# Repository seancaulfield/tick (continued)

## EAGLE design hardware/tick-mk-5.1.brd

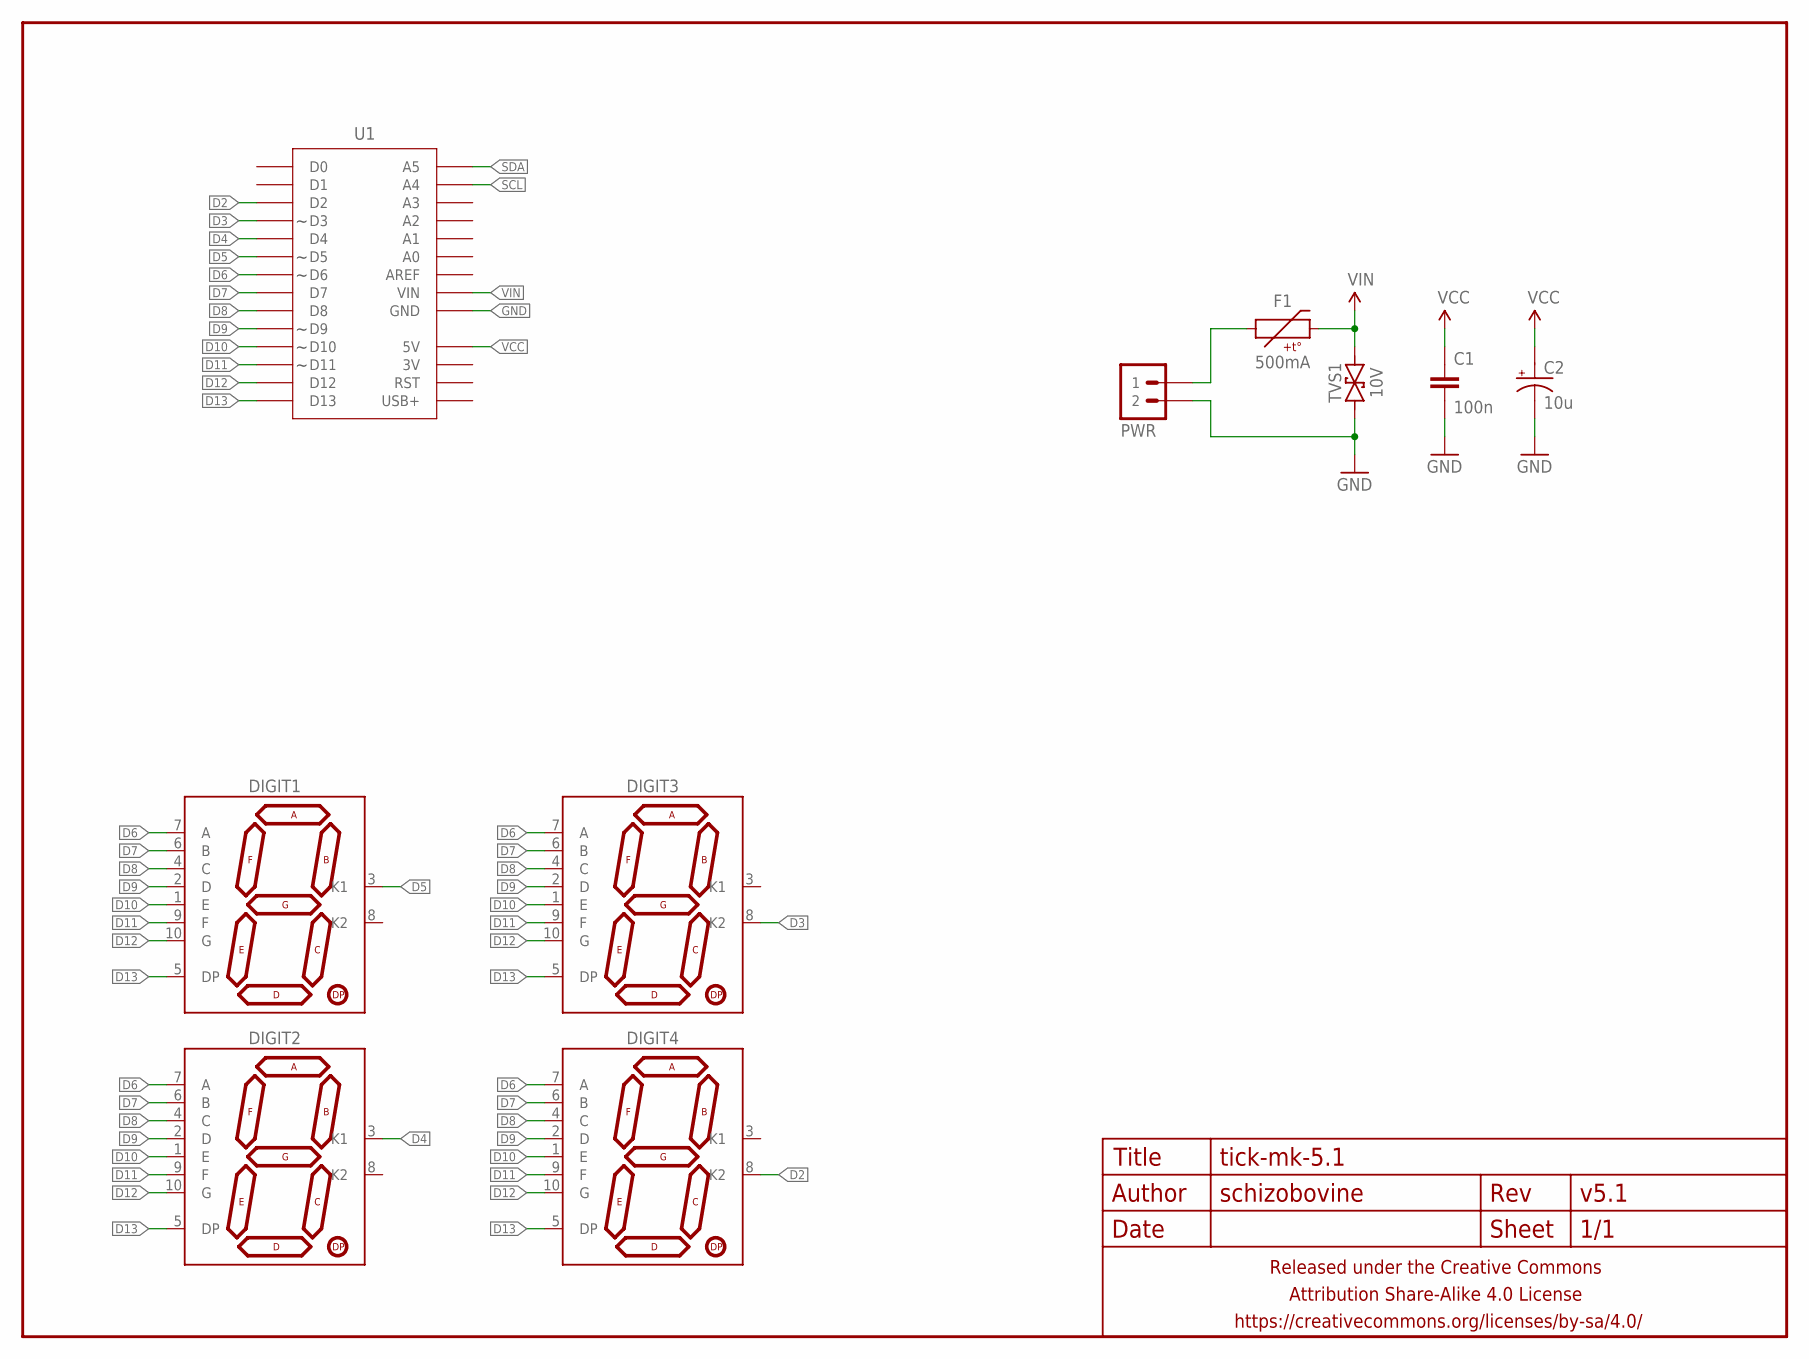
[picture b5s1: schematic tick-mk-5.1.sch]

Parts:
C1: 100n; C025-024X044
C2: 10u; E2-5
DIGIT1, DIGIT2, DIGIT3, DIGIT4: 7SEG_1DIGPTH-25.4MM-BARE; 7SEG_1DIG_25.4MM_NOSILK
F1: 500mA; PTC-PTH-5.08MM
FRAME1: FRAME-LETTERNO_PACKAGE; DUMMY
PWR: M02JST-PTH-VERT; JST-2-PH-VERT-PTH
TVS1: 10V; DO-41-TVS-BI-10.16MM
U1: ADAFRUIT_METRO_MININOHOLES-NOOUTLINE-SILK; ADAFRUIT_METRO_MINI

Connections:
D2: DIGIT4.8 (K2), U1.3 (D2)
D3: DIGIT3.8 (K2), U1.4 (D3)
D4: DIGIT2.3 (K1), U1.5 (D4)
D5: DIGIT1.3 (K1), U1.6 (D5)
D6: DIGIT1.7 (A), DIGIT2.7 (A), DIGIT3.7 (A), DIGIT4.7 (A), U1.7 (D6)
D7: DIGIT1.6 (B), DIGIT2.6 (B), DIGIT3.6 (B), DIGIT4.6 (B), U1.8 (D7)
D8: DIGIT1.4 (C), DIGIT2.4 (C), DIGIT3.4 (C), DIGIT4.4 (C), U1.9 (D8)
D9: DIGIT1.2 (D), DIGIT2.2 (D), DIGIT3.2 (D), DIGIT4.2 (D), U1.10 (D9)
D10: DIGIT1.1 (E), DIGIT2.1 (E), DIGIT3.1 (E), DIGIT4.1 (E), U1.11 (D10)
D11: DIGIT1.9 (F), DIGIT2.9 (F), DIGIT3.9 (F), DIGIT4.9 (F), U1.12 (D11)
D12: DIGIT1.10 (G), DIGIT2.10 (G), DIGIT3.10 (G), DIGIT4.10 (G), U1.13 (D12)
D13: DIGIT1.5 (DP), DIGIT2.5 (DP), DIGIT3.5 (DP), DIGIT4.5 (DP), U1.14 (D13)
GND: C1.2, C2.-, PWR.2, TVS1.P$1 (1), U1.19 (GND), U1.20 (GND)
unnamed: F1.P$1 (1), PWR.1
SCL: U1.27 (A4)
SDA: U1.28 (A5)
VCC: C1.1, C2.+, U1.18 (5V)
VIN: F1.P$2 (2), TVS1.P$2 (2), U1.21 (VIN)

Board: 2 copper layers, 15 parts (5 on the bottom side), 16 nets, no tracks yet.

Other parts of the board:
U$1: TICK_SYMBOL
U$2: COW_SMALL
U$4: CC-BY-SA-4.0-NO-URL
U$5: OSHWLOGO_TOP_0.2

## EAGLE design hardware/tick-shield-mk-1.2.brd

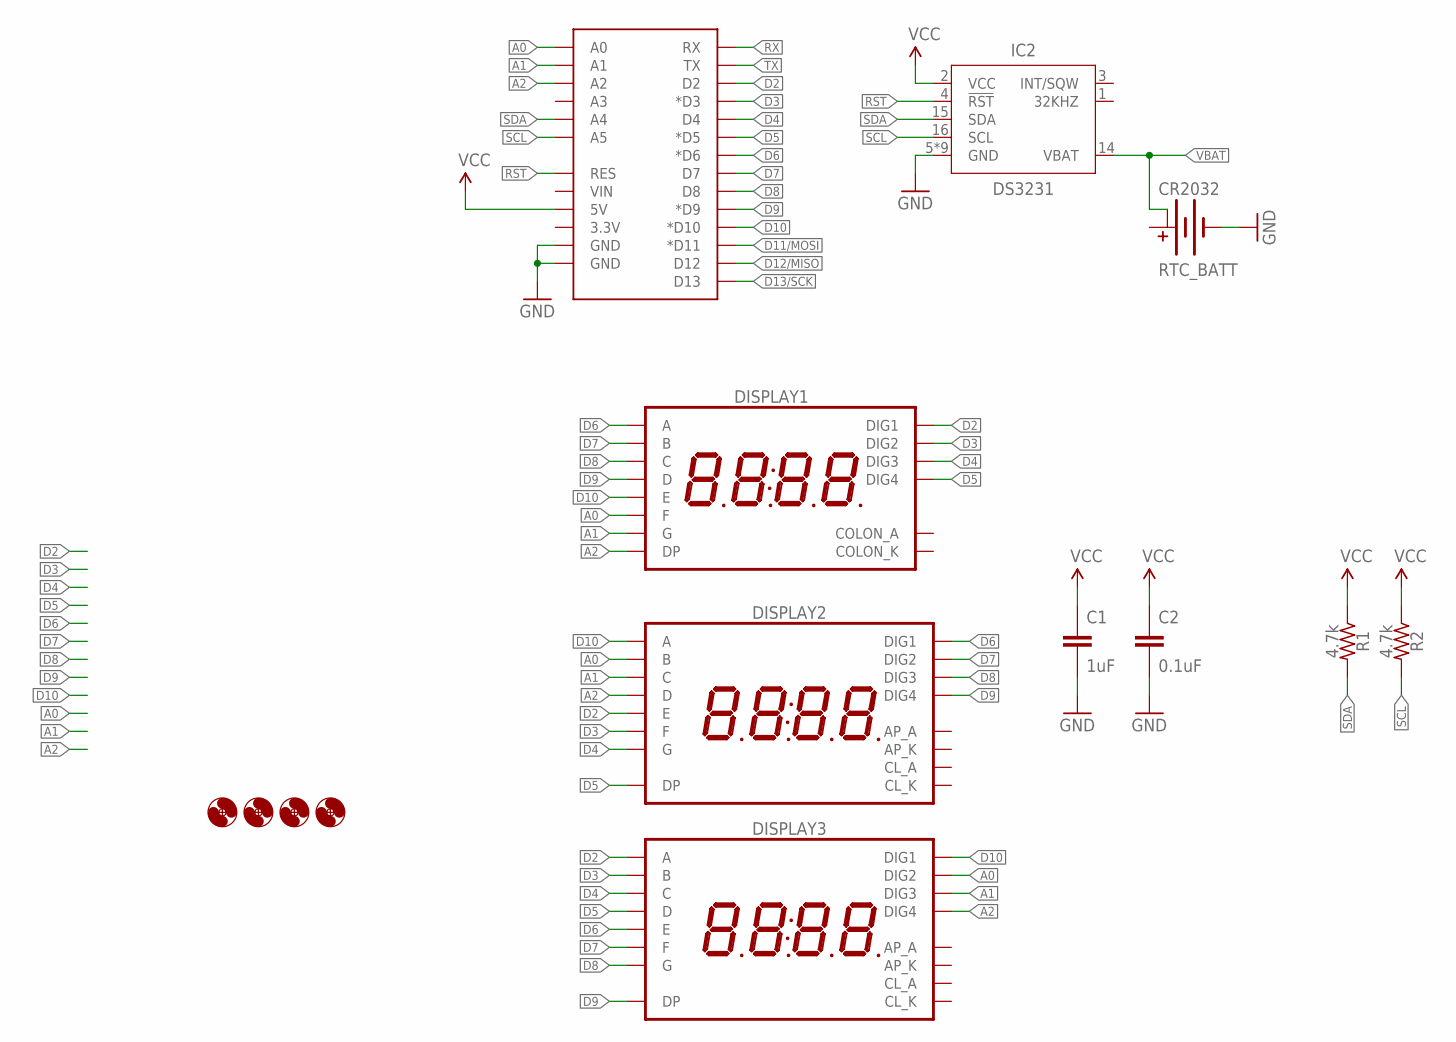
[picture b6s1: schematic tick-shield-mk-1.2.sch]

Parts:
C1: 1uF; C025-024X044
C2: 0.1uF; C0805
DISPLAY1: 7SEG_4DIGIT_COLON14.2MM-CC-NS; 7SEG_4DIG_NS
DISPLAY2, DISPLAY3: 7SEG_4DIGIT_COLON_APOS; 7SEG_4DIG_10MM
H1, H2, H3, H4: HOLE#2; HOLE-#2
IC2: DS3231; SO16W
R1, R2: 4.7k; RESISTOR-AXIAL-PTH-6.35MM
RTC_BATT: CR2032; BATTCON_20MM_MINE
U$1: ARDUINO_SHIELD_SMALLER; ARDUINO_SHIELD_NOOUTLINE_INSIDE_SMALLER

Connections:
A0: DISPLAY1.P$12 (F), DISPLAY2.16 (B), DISPLAY3.2 (DIG2), U$1.A0
A1: DISPLAY1.P$5 (G), DISPLAY2.13 (C), DISPLAY3.6 (DIG3), U$1.A1
A2: DISPLAY1.P$3 (DP), DISPLAY2.3 (D), DISPLAY3.8 (DIG4), U$1.A2
D2: DISPLAY1.P$14 (DIG1), DISPLAY2.5 (E), DISPLAY3.14 (A), U$1.D2
D3: DISPLAY1.P$11 (DIG2), DISPLAY2.11 (F), DISPLAY3.16 (B), U$1.D3 (*D3)
D4: DISPLAY1.P$10 (DIG3), DISPLAY2.15 (G), DISPLAY3.13 (C), U$1.D4
D5: DISPLAY1.P$6 (DIG4), DISPLAY2.7 (DP), DISPLAY3.3 (D), U$1.D5 (*D5)
D6: DISPLAY1.P$13 (A), DISPLAY2.1 (DIG1), DISPLAY3.5 (E), U$1.D6 (*D6)
D7: DISPLAY1.P$9 (B), DISPLAY2.2 (DIG2), DISPLAY3.11 (F), U$1.D7
D8: DISPLAY1.P$4 (C), DISPLAY2.6 (DIG3), DISPLAY3.15 (G), U$1.D8
D9: DISPLAY1.P$2 (D), DISPLAY2.8 (DIG4), DISPLAY3.7 (DP), U$1.D9 (*D9)
D10: DISPLAY1.P$1 (E), DISPLAY2.14 (A), DISPLAY3.1 (DIG1), U$1.D10 (*D10)
D11/MOSI: U$1.D11 (*D11)
D12/MISO: U$1.D12
D13/SCK: U$1.D13
GND: C1.2, C2.2, IC2.5 (GND), IC2.6 (GND), IC2.7 (GND), IC2.8 (GND), IC2.9 (GND), IC2.10 (GND), IC2.11 (GND), IC2.12 (GND), IC2.13 (GND), RTC_BATT.BOTTOM (-), U$1.GND@0 (GND), U$1.GND@1 (GND)
RST: IC2.4 (!RST), U$1.RES
RX: U$1.RX
SCL: IC2.16 (SCL), R2.P$2 (2), U$1.A5
SDA: IC2.15 (SDA), R1.P$2 (2), U$1.A4
TX: U$1.TX
VBAT: IC2.14 (VBAT), RTC_BATT.TOP@2 (+1)
VCC: C1.1, C2.1, IC2.2 (VCC), R1.P$1 (1), R2.P$1 (1), U$1.5V

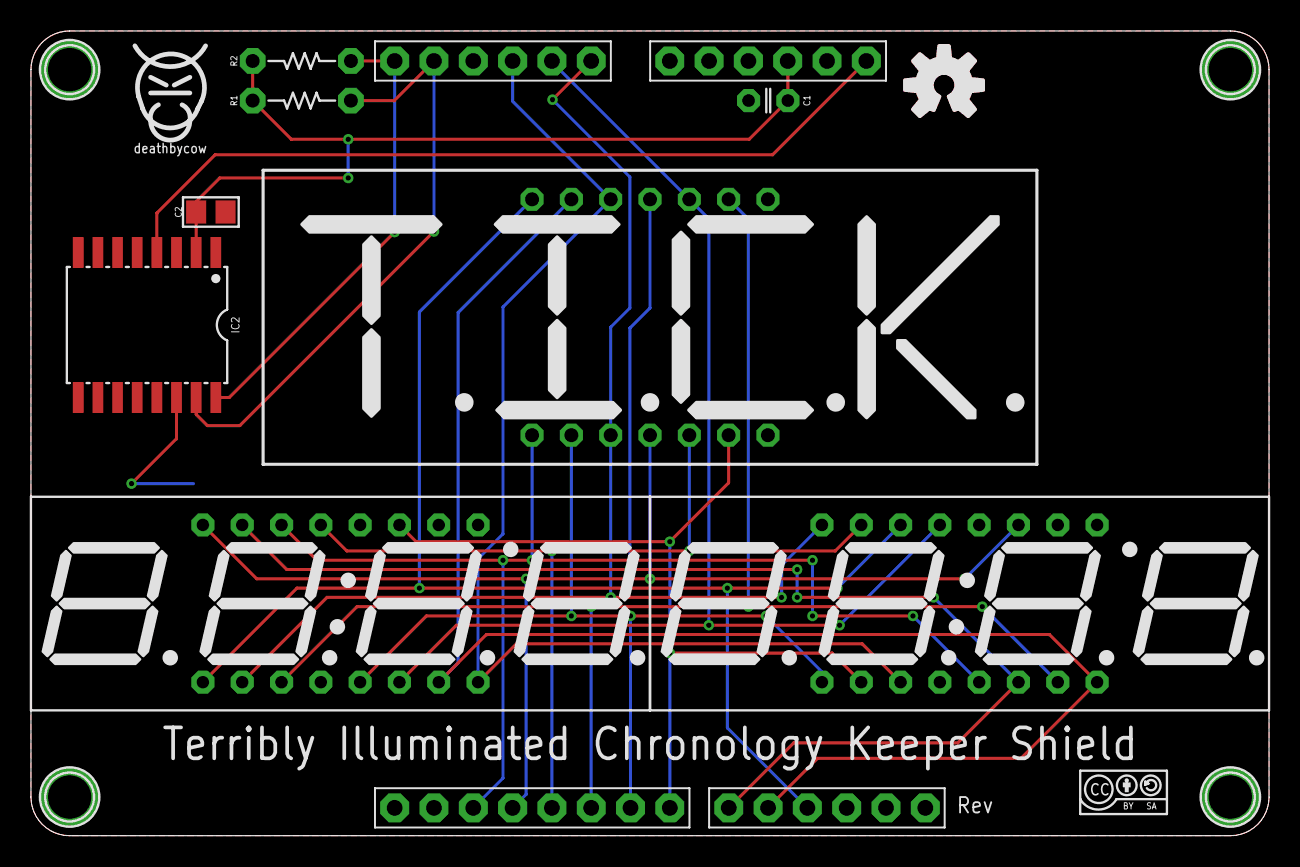
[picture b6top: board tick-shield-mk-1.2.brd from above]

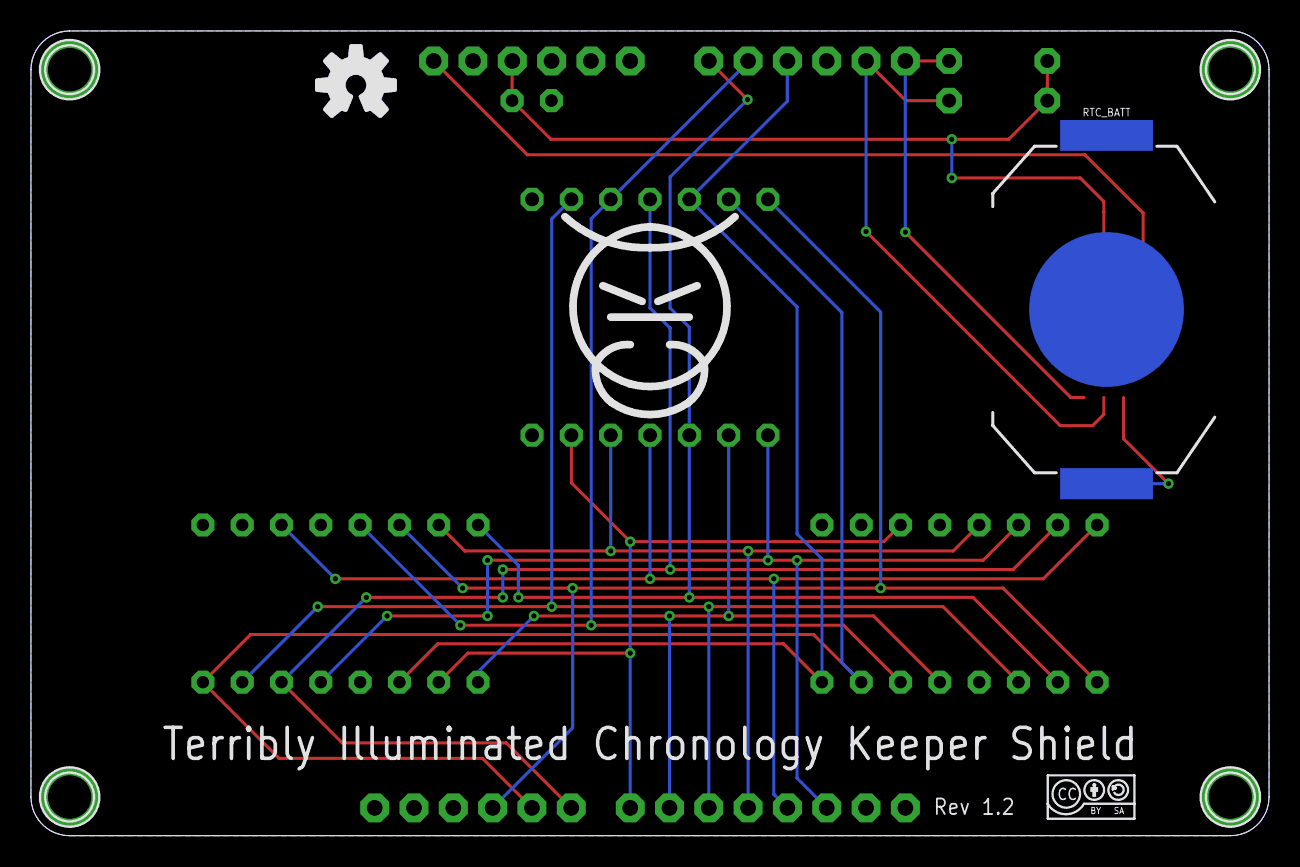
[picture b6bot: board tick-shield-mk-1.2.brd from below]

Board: 2 copper layers, 80.0 x 52.0 mm, 21 parts (4 on the bottom side), 18 nets.

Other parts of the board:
U$2: TICK_SYMBOL_0.56
U$3, U$4: CC-BY-SA-4.0-NO-URL
U$5: COW
U$6: COW_SMALL
U$7, U$8: OSHWLOGO_TOP_0.2_A
